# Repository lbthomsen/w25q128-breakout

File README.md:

# w25q128-breakout
W25Q128 Breakout Board

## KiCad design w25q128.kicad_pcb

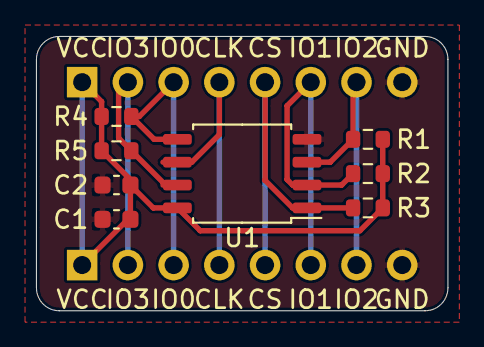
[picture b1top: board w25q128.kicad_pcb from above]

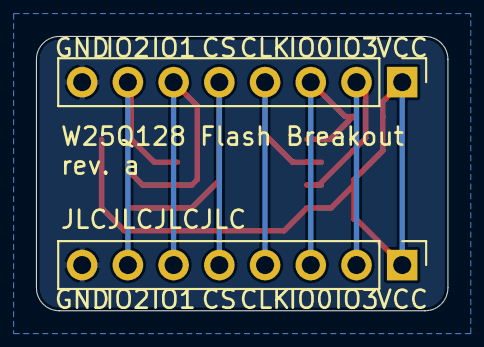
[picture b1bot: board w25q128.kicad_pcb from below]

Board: 2 copper layers, 22.9 x 15.2 mm, 10 parts (2 on the bottom side), 8 nets.

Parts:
C1: 4.7uF; C_0603_1608Metric
C2: 100nF; C_0603_1608Metric
J1, J2: PinHeader_1x08_P2.54mm_Vertical
R1, R2, R3, R4, R5: 2k2; R_0603_1608Metric
U1: W25Q128JVS; SOIC-8_5.23x5.23mm_P1.27mm

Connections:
CLK: J1.4, J2.4, U1.6
CS: J1.5, J2.5, R3.2, U1.1
GND: C1.2, C2.2, J1.8, J2.8, U1.4
IO0: J1.3, J2.3, R4.2, U1.5
IO1: J1.6, J2.6, R2.2, U1.2
IO2: J1.7, J2.7, R1.2, U1.3
IO3: J1.2, J2.2, R5.2, U1.7
VCC: C1.1, C2.1, J1.1, J2.1, R1.1, R2.1, R3.1, R4.1, R5.1, U1.8

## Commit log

2021-05-29 Kind of done
2021-05-30 Hmmm
